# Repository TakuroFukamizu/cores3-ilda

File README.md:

# CoreS3 ILDA

M5Stack CoreS3を使うILDA評価基板と、今後開発する制御ソフトウェアを管理するモノレポです。

## 構成

```text
hardware/rev-a/       Rev.Aの設計説明・部品表
  kicad/             編集するKiCadプロジェクト・回路図・PCB・ローカルライブラリ
firmware/            CoreS3向けファームウェア（未実装）
software/            PC側ツール／アプリ（未実装）
docs/                共通仕様・設計判断
releases/rev-a/       製造・評価時点の生成物と検査記録
build/               作業用の生成物（Git管理外）
```

まず [ハードウェアREADME](hardware/rev-a/README.md) を読んでください。KiCad 10で `hardware/rev-a/kicad/CoreS3_ILDA_RevA.kicad_pro` を開きます。ライブラリはプロジェクト相対参照で同梱しています。

## Git運用

- 回路図・PCB・プロジェクト設定・ライブラリ・BOM・文書・ソースコードをコミットします。
- 通常のGerber、プレビュー、ビルド成果物は `build/` に出力します。KiCadの個人設定、ロック、バックアップは除外します。
- 製造に使用する生成物だけを `releases/<revision>/<date>/` に保存し、その設計と同じコミットで確定します。初回分は2026-10-02の記録です。
- 基板リビジョンを変更する際は `hardware/rev-b/` 等を作り、旧版を保持します。同じリビジョン内の調整はGit履歴で管理します。
- ファームウェアのフレームワーク、依存管理、CI、リモートリポジトリはまだ選定していません。

## 変更後の検証

KiCadでERCとDRC（回路図との一致検査を含む）を再実行し、ゾーンを再フィルして保存してください。CLIをPATHへ設定している場合のPowerShell例：

```powershell
New-Item -ItemType Directory -Force build/rev-a | Out-Null
kicad-cli sch erc --format json -o build/rev-a/ERC.json hardware/rev-a/kicad/CoreS3_ILDA_RevA.kicad_sch
kicad-cli pcb drc --format json --schematic-parity -o build/rev-a/DRC.json hardware/rev-a/kicad/CoreS3_ILDA_RevA.kicad_pcb
```

初回の検査はERC/DRC/未配線/回路図不一致0件ですが、実機動作と機械的嵌合は未検証です。初回電気評価はレーザー未接続で実施してください。制御ソフトウェアには起動時ENABLE Low、DAC初期値、異常時停止の実装が必要です。

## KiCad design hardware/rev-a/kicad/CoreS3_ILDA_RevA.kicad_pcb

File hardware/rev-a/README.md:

# CoreS3 ILDA評価基板 Rev.A

2026-10-02 / KiCad 10.0.6 / 2層・280 × 202.84 mm。手はんだと測定を優先した試作設計です。回路図ERC、PCB DRC、回路図とPCBの一致検査はすべて問題0件。実基板での動作・熱・ノイズ・機械的嵌合は未検証です。

## 開くファイル・発注データ

編集対象はこのフォルダの `kicad/` とBOMです。以下の製造データ・プレビュー・検証結果はリポジトリルートの `releases/rev-a/2026-10-02/` に保存した初回設計時点の記録です。設計変更後は再生成し、古い検査結果を流用しないでください。

- `kicad/CoreS3_ILDA_RevA.kicad_pro` をKiCad 10で開く。回路図はルート＋13子シート。ローカルシンボル・フットプリントを同梱。
- `manufacturing/`：表裏銅箔、表裏マスク、表裏シルク、外形Gerber、PTH/NPTH Excellonドリル、ドリル図。
- `BOM.csv`：部品別明細。`BOM_grouped.csv`：同一部品の集計。DNPは標準構成では未実装。
- `assembly-top.svg`：部品配置・機械形状。`board-top.png`：配線プレビュー。`schematic_svg/`：全回路図プレビュー。
- `verification/`：検査結果と理想DC解析。基板発注設定の目安はFR-4、1.6 mm、2層、銅厚1 oz、両面ソルダーマスク。製造会社の加工条件にも照合してください。

J1のM5-BusはM5Stack公式CoreS3 Module Type Aデータ由来の**表面実装**パターンです。調達候補はM5Stack **A117 / Bus Socket SMD 13.2**。一般的な2×15スルーホールソケットとは互換ではありません。CoreS3本体投影は50×50 mm、位置決め穴と支持穴を設けています。基板の下面へのバス貫通実装はありません。発注前に配置図を原寸印刷し、購入するコネクタ・CoreS3底部と合わせてください。ケース、底部モジュール、スペーサー高さによる干渉は実物確認が必要です。

## 回路構成

MCP4922-E/P×3を3.3V駆動し、共通2.048V基準・共通LDACで6chを更新します。NJM4580DD×4でX/Y差動、RGBのGND基準出力、1.024V中点バッファを構成します。RGBの能動差動には追加NJM4580×2が必要なため、U9/U10と関連部品をオプション実装にしました。

5VからMCW03-05D12で±12Vを生成。AGNDとDGNDは連続した共通GNDプレーンです。DC/DCの出力COMもGNDへ接続するため、この基板全体はガルバニック絶縁されません。SPI配線下のGNDを分断せず、DAC基準とアナログ回路を電源・リレーから分離して配置しています。各ICの電源に100nF、基準に1µFと分散100nFを配置しています。

### 電源・実装

- J2：安定化5V入力。2A供給可能な電源を推奨。極性はシルクと回路図で確認。
- JP1：**1–2＝外部5V（標準）／2–3＝M5-Bus 5V**。同時短絡禁止。標準構成ではCoreS3をUSB等から別途給電します。バス給電はCoreS3側電源容量を確認してから使用。
- F1：基板上の端子台に、絶縁した外付けヒューズホルダー＋T2Aヒューズを接続します。単なるワイヤーで置換しないでください。
- J2/J3/J4/F1の端子台ピッチは**5.00 mm**。5.08 mm品の無理な装着は避け、フットプリントに一致する品を購入。
- R1/R2＝330Ω・2Wは各±12V出力の最小負荷確保用。約36mA／0.44Wを消費するので基板から約5mm浮かせて実装。熱くなります。
- MCW03の各レールは125mA定格。6個のオペアンプを実装した場合、無負荷時の保守的な見積りは負荷抵抗36mA＋オペアンプ54mA＝約90mA/レール。外部負荷分も含めて確認してください。出力コンデンサは各22µF＋デカップリングで、メーカーの容量性負荷上限100µF/レール以内です。
- C4は**プラス側がGND、マイナス側が−12V**。C1は16V以上（25V品も外径6.3mm・ピッチ2.5mmに適合すれば可）、C3/C4は25V以上。
- MCP1501はSOT23-6、Q1はSOT23です。DIP部品のほか、この2点とM5-Busは表面実装が必要です。
- DB25は秋月DMR-25SGG用の専用パターン。外部パネルとねじ／ケーブル支持を併用し、はんだ接合だけにケーブル荷重を掛けないでください。

## CoreS3ピン割当

|機能|GPIO|M5-Busピン|
|---|---:|---:|
|MOSI|G37|7|
|SCK|G36|11|
|CS：X/Y（U1）|G5|8|
|CS：R/G（U2）|G6|21|
|CS：B/I（U3）|G7|22|
|共通LDAC_N|G8|4|
|ENABLE（Highでリレー許可）|G10|2|
|予備、JP2へ|G9|10|
|3V3|—|12|
|5V|—|28|
|GND|—|1、3、5|

LCD・SDとSPIを共有します。LCD CS＝G3、SD CS＝G4を非選択にし、SPIトランザクションを排他制御してください。DAC連続転送中に画面・SDアクセスを割り込ませない構成から評価します。JP2は通常OPEN。

## DAC設定とアナログ出力

MCP4922のVREF A/Bは2.048V、VDDは3.3V。初期設定はSPI mode 0、MSB first、16bit、1MHz。BUF=0（基準入力アンバッファ）、GA=1（利得1）、SHDNビット=1（動作）です。

```text
Channel A command = 0x3000 | (code & 0x0FFF)
Channel B command = 0xB000 | (code & 0x0FFF)
6chを各CSで書き込み → 全CSをHigh → 共通LDACをLow 1µs → High
```

DAC出力はcode×0.5mV、最大code4095で2.0475Vです。ハードウェアSHDN（pin9）はDAC_RUNでプルアップ、JP3は通常OPEN。**JP3短絡によるSHDNはX/Yの中央保持にはなりません**。出力が高インピーダンスとなり、後段で偏った位置へ動く可能性があります。レーザーOFFにはENABLE／ARM回路を使用します。

|出力|公称式・範囲（出力抵抗前）|
|---|---|
|X+/Y+|4.7×(VDAC−1.024V)、約−4.813〜+4.810V|
|X−/Y−|対応する＋出力の反転|
|X/Y差動|約−9.626〜+9.621V、code2048で0V|
|RGB GND基準|2.42×VDAC、0〜4.955V|
|RGB能動差動|＋側1.22×VDAC、−側その反転、差分0〜4.996V|

出力の各線に100Ωを入れています。RGBはリレー出力側に10kΩのプルダウンもあるため、外部無負荷でもDB25側の公称最大差分はGND基準約4.906V／能動差動約4.946Vです。プロジェクタの入力負荷でさらに変わります。抵抗は調達しやすい1%品を基本としたため、中心・利得は実測校正してください。公差を含む最大値は公称値を超え得ます。初期ソフト上限はRGB code3900以下から始め、実測して5V差動を超えない範囲に設定します。

±12V電源に対して、オペアンプ入出力には十分な公称余裕を取っています。ただしデータシートの主な保証条件は±15Vであり、±12Vでの実負荷・過渡応答・クリッピングは実測対象です。DACのセトリング4.5µsは代表値です。25k点/sのシステム性能を保証するものではありません。まず1k点/sで確認し、SPIクロック4〜8MHzなどへの変更後に全ch転送時間とアナログ整定を測定してください。

### RGBジャンパ（電源OFFで変更）

|モード|JP4/JP6/JP8（R/G/B利得）|JP5/JP7/JP9（R/G/B負側）|追加部品|
|---|---|---|---|
|標準：GND基準|OPEN|1–2|なし、U5〜U8の4個|
|能動差動|CLOSED|2–3|U9/U10、C24〜C27、R41〜R49をすべて実装|

利得と負側選択は必ず同時に変更します。GND基準利得のまま負側を反転にすると、差動振幅が過大になります。追加2個のうち余ったアンプはGND追従バッファとして終端しています。

## ARMとDB25

J3に維持型NO接点のARMスイッチ（できればキー式）、J4にNC接点の外部非常停止ループを接続します。ARM閉・非常停止ループ閉・G10 Highのすべてが成立したときだけ、4個の5Vリレーが励磁します（コイル合計約160mA）。G10は外付けプルダウンを設けています。

非励磁時はRGB±をGNDへ接続、シャッターは0V、インターロック4–17は開放です。励磁時にRGBをアナログ出力へ切替、シャッターを5V、インターロックを閉じます。これは起動・手動停止用で、点ごとの高速ブランキングにはRGBのDACデータを使用します。リレーとフライバックダイオードのため停止には遅延があります。

**このRev.Aには独立ウォッチドッグ、走査停止検知、±12V監視、接点溶着監視はありません。CPUがENABLE Highのまま停止した場合や接点故障時の停止は保証できません。** プロジェクタ本体のキー・非常停止・シャッター等も有効にして評価してください。実機のX-RGB 705の入力回路・停止動作は未確認であり、ILDA DB25があることだけで互換性を保証していません。

各使用信号の直前に独立切り離しジャンパを設けています。**初回はJP10〜JP25をすべてOPEN**。未使用DB25ピンはNCです。

|ジャンパ|DB25ピン|信号|
|---|---:|---|
|JP10 / JP18|1 / 14|X+ / X−|
|JP11 / JP19|2 / 15|Y+ / Y−|
|JP12 / JP20|3 / 16|Intensity+ / Intensity−|
|JP13 / JP21|4 / 17|Interlock A / B|
|JP14 / JP22|5 / 18|R+ / R−|
|JP15 / JP23|6 / 19|G+ / G−|
|JP16 / JP24|7 / 20|B+ / B−|
|JP17|12|Shutter|
|JP25|25|信号GND|

第6DACは予備IntensityとしてTP6とJ6 pin1に引き出しています。**Intensity用出力アンプは未実装**です。J6は1＝DAC_I、2＝I+、3＝I−、4＝GNDの外部変換回路接続用。外部回路を追加しない場合はJP12/JP20をOPENのまま使用してください。DAC_IをDB25へ直接接続しないでください。

ケーブルは全ピン直結のILDA用を使用し、両端の性別と導通を確認します。RS-232ヌルモデム／クロスケーブルは使用しません。DB25シェルはこの部品ではPCB接地されません。筐体・シールドの接地は装置側条件に合わせて別途検討します。

## テストポイント

|番号|信号|
|---|---|
|TP1〜TP6|DAC_X、DAC_Y、DAC_R、DAC_G、DAC_B、DAC_I|
|TP7〜TP10|X+、X−、Y+、Y−|
|TP11〜TP16|R+、R−、G+、G−、B+、B−（リレー後、DB25切離し前）|
|TP17 / TP18|VREF 2.048V / VCENTER 1.024V|
|TP19 / TP20|+12V / −12V|
|TP21 / TP22|3V3 / 5V|
|TP23|AGND（共通GND）|
|TP24 / TP25 / TP26|Shutter / ENABLE GPIO / コイル5V|

## 初期評価手順

1. **プロジェクタ・レーザーを接続せずに開始。** はんだ・電源短絡・電解極性・DIP向き・J1嵌合を点検。JP1＝1–2、JP2/JP3＝OPEN、RGB＝GND基準、JP10〜25＝OPEN、ARM＝OFF。
2. 電流制限付き5V電源でJ2へ給電し、5Vと±12Vを確認。R1/R2の発熱を確認し、異常な温度や消費電流があれば停止。CoreS3を別途給電し、3V3、VREF、VCENTERを測定。
3. ファームウェアの最初にENABLE Low、すべてのCSとLDAC Highを設定。表示初期化より先に行う。X/Y＝2048、R/G/B/I＝0を全chへ書き込み、LDACで反映。ARM OFFでRGB±≒0V、シャッター0V、インターロック開放を確認。
4. まだプロジェクタ未接続のままARM ON／ENABLE Highを試験。各DACの0・2048・4095を測定し、X/Y中心と極性、RGB利得を確認。RGB上限を校正。負荷模擬抵抗とオシロスコープで整定・オーバーシュート・ノイズを確認。
5. ENABLE Low、ARM OFF、非常停止、CoreS3リセット・電源断の各操作でRGB接地／シャッターOFF／インターロック開放へ戻るか確認。電源投入順序を変えた試験も実施。差動信号の負側に接地型オシロスコープのGNDクリップを接続しないこと。両チャンネルのGNDは共通GNDとし、差分演算または差動プローブを使う。
6. 電源OFF後に必要なDB25ジャンパを閉じる。Intensityは未使用ならOPEN。X-RGB 705の説明書・ケーブル導通・入力負荷と各停止機能を確認したうえで接続。最初はRGB＝0、XY＝中央。実光を扱う評価は光路を遮蔽し、機器に適した管理下で行う。
7. 小振幅XY（2048±102程度）、低い点更新速度から開始。異常・バッファ欠落時はENABLEをLowへ。安定後に速度・振幅を上げ、中心・最大振幅・RGB黒レベルを保存して校正。

## 検証範囲・調達

`verification/ERC.json` はERC指摘0件、`DRC.json` は違反0件・未接続0件・回路図一致問題0件です。プロジェクト固有の違反除外は使用していません。KiCad標準の無効チェック項目はDRC JSONに列挙されています。`nominal_dc.csv` は実際の接続・抵抗値を使った理想オペアンプの節点解析で、X/YとRGBのDC式を6条件で照合した結果です。実機試験、部品公差解析、過渡SPICE解析、EMC試験、安全認証の代わりではありません。

主要部品は秋月の商品・データシートを確認しました。価格・在庫は変動します。M5-Bus SMDコネクタ、完全一致の5.00mm端子台、外部ARMスイッチ・非常停止・ヒューズなどは別途調達対象です。抵抗の例：10kΩ＝108550、47kΩ＝108560、2.2kΩ＝108540、12kΩ＝108551。寸法・ピッチ・定格もBOMフットプリントと照合してください。

基板外の付属品：5V/2A電源、T2Aヒューズと絶縁ホルダー、維持型NO ARMスイッチ、NC非常停止スイッチ、2.54mmジャンパキャップ、絶縁スペーサー、適合する全ピン直結ILDAケーブル。任意でDIP14ソケット3個、DIP8ソケット4個（差動オプション時6個）。

## 設計時に確認した資料

- [M5Stack CoreS3公式ピンマップ](https://docs.m5stack.com/en/core/CoreS3)
- [公式CoreS3 M5-Bus基板データ](https://github.com/m5stack/M5_Hardware/blob/master/Common/Module_Type_A/Footprints/Module_Type_A_CoreS3_M5_Bus.PcbDoc)
- [M5Stack A117 SMD Bus Socket](https://shop.m5stack.com/products/2-%E2%9C%96-15-pinheader-bus-socket-smd-for-13-2-module-10-sets)
- [MCP4921/4922](https://akizukidenshi.com/goodsaffix/MCP4921_2.pdf)
- [MCP1501](https://akizukidenshi.com/goodsaffix/mcp1501_j.pdf)
- [NJM4580](https://akizukidenshi.com/goodsaffix/NJM4580_j.pdf)
- [MCW03 DC/DC](https://akizukidenshi.com/goodsaffix/MCW03.pdf)
- [DMR-25SGG外形](https://akizukidenshi.com/goodsaffix/DMR-25SGG.pdf)
- [HFD27リレー](https://akizukidenshi.com/goodsaffix/HFD27.pdf)
- [IRLML6344](https://akizukidenshi.com/goodsaffix/irlml6344pbf.pdf)
- [ILDA ISP-99 rev002](https://www.ilda.com/resources/StandardsDocs/ILDA_ISP99_rev002.pdf)

### 2026-10-06 回路図の表示改訂

部品ごとのラベル接続を、機能別に配置した実線主体の回路図へ変更しました。電源、ホスト、基準・中点、DAC、X、Y、R、G、B、ARM、リレー、DB25、オペアンプ電源の13シート＋目次です。テストポイントは各回路へ移動しました。ファイル名は既存参照との連続性のため一部旧名称を維持しています。全160部品・135ネットの接続およびPCBの物理配線は変更していません。PCBは回路図への参照パスだけを同期しています。初回releases配下の回路図プレビューは改訂前の記録です。

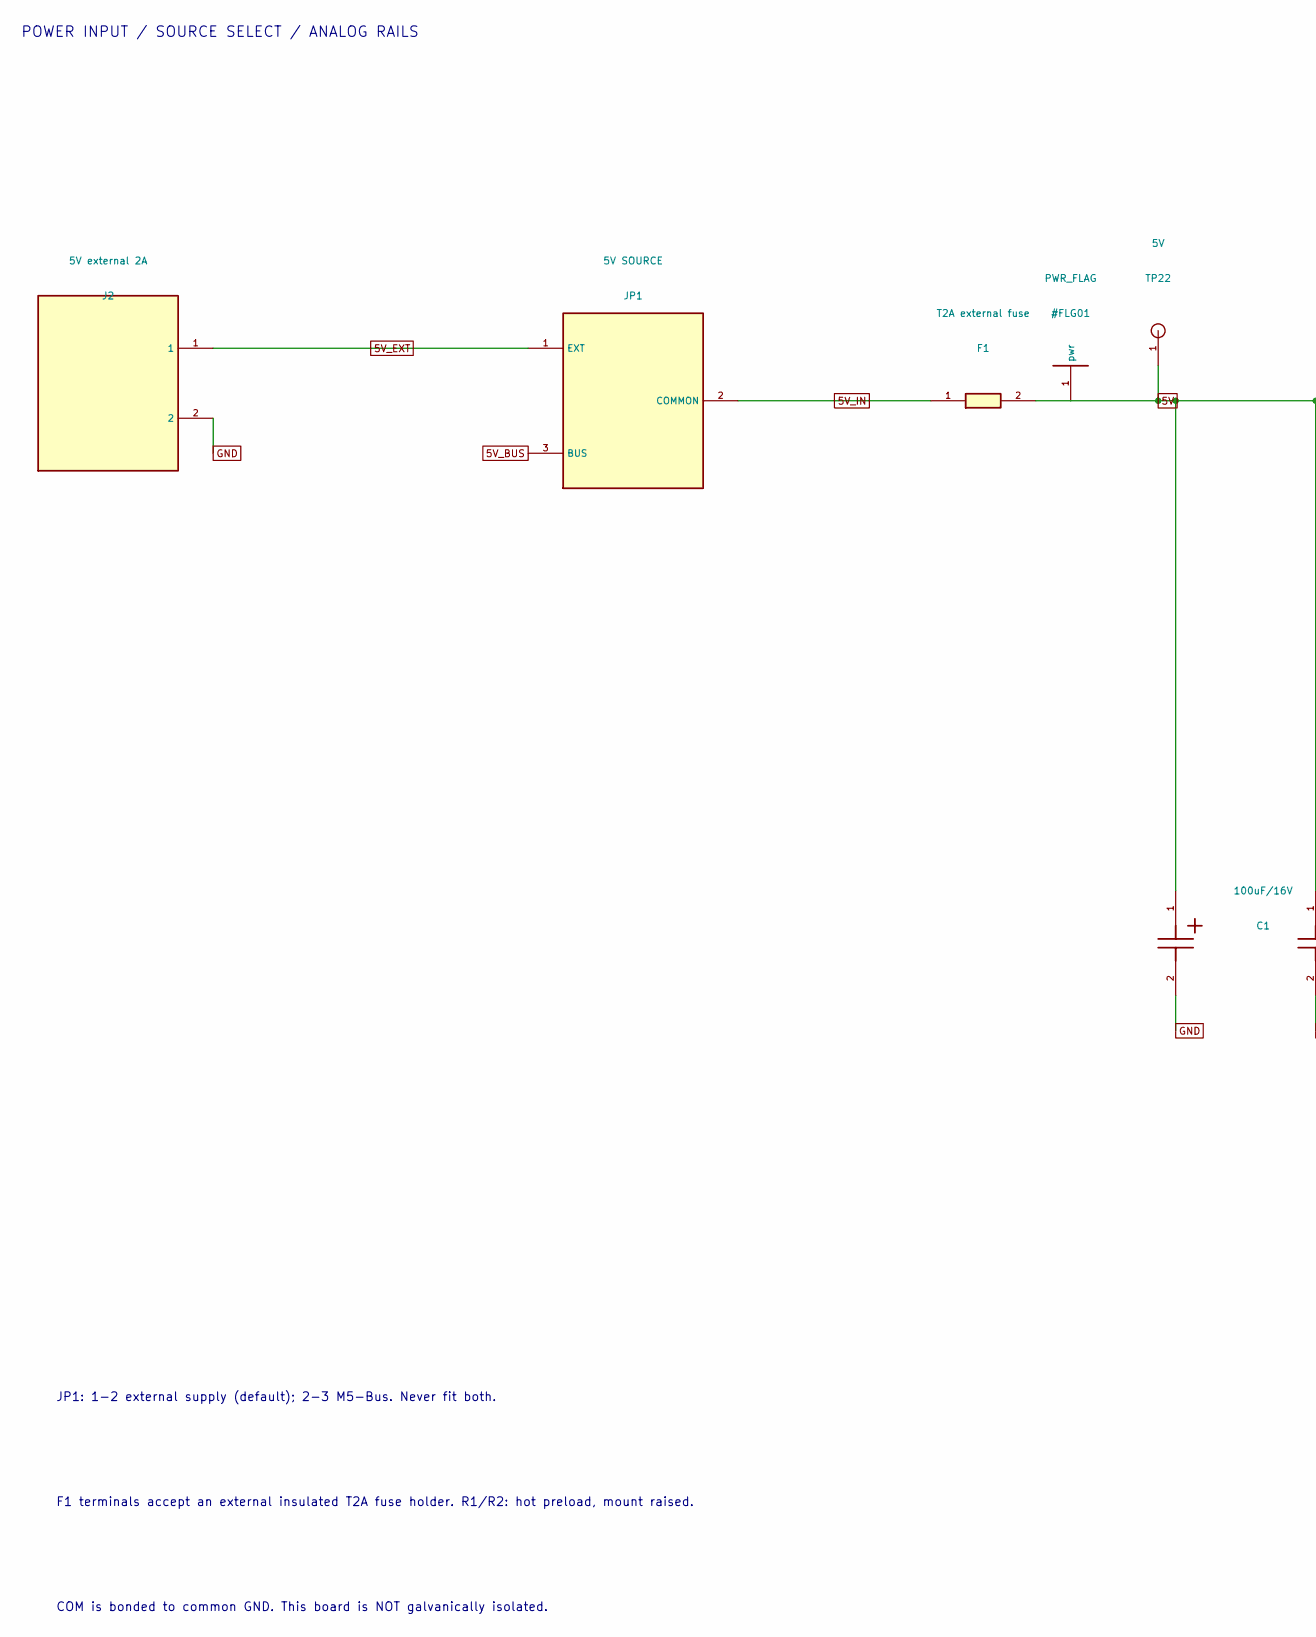
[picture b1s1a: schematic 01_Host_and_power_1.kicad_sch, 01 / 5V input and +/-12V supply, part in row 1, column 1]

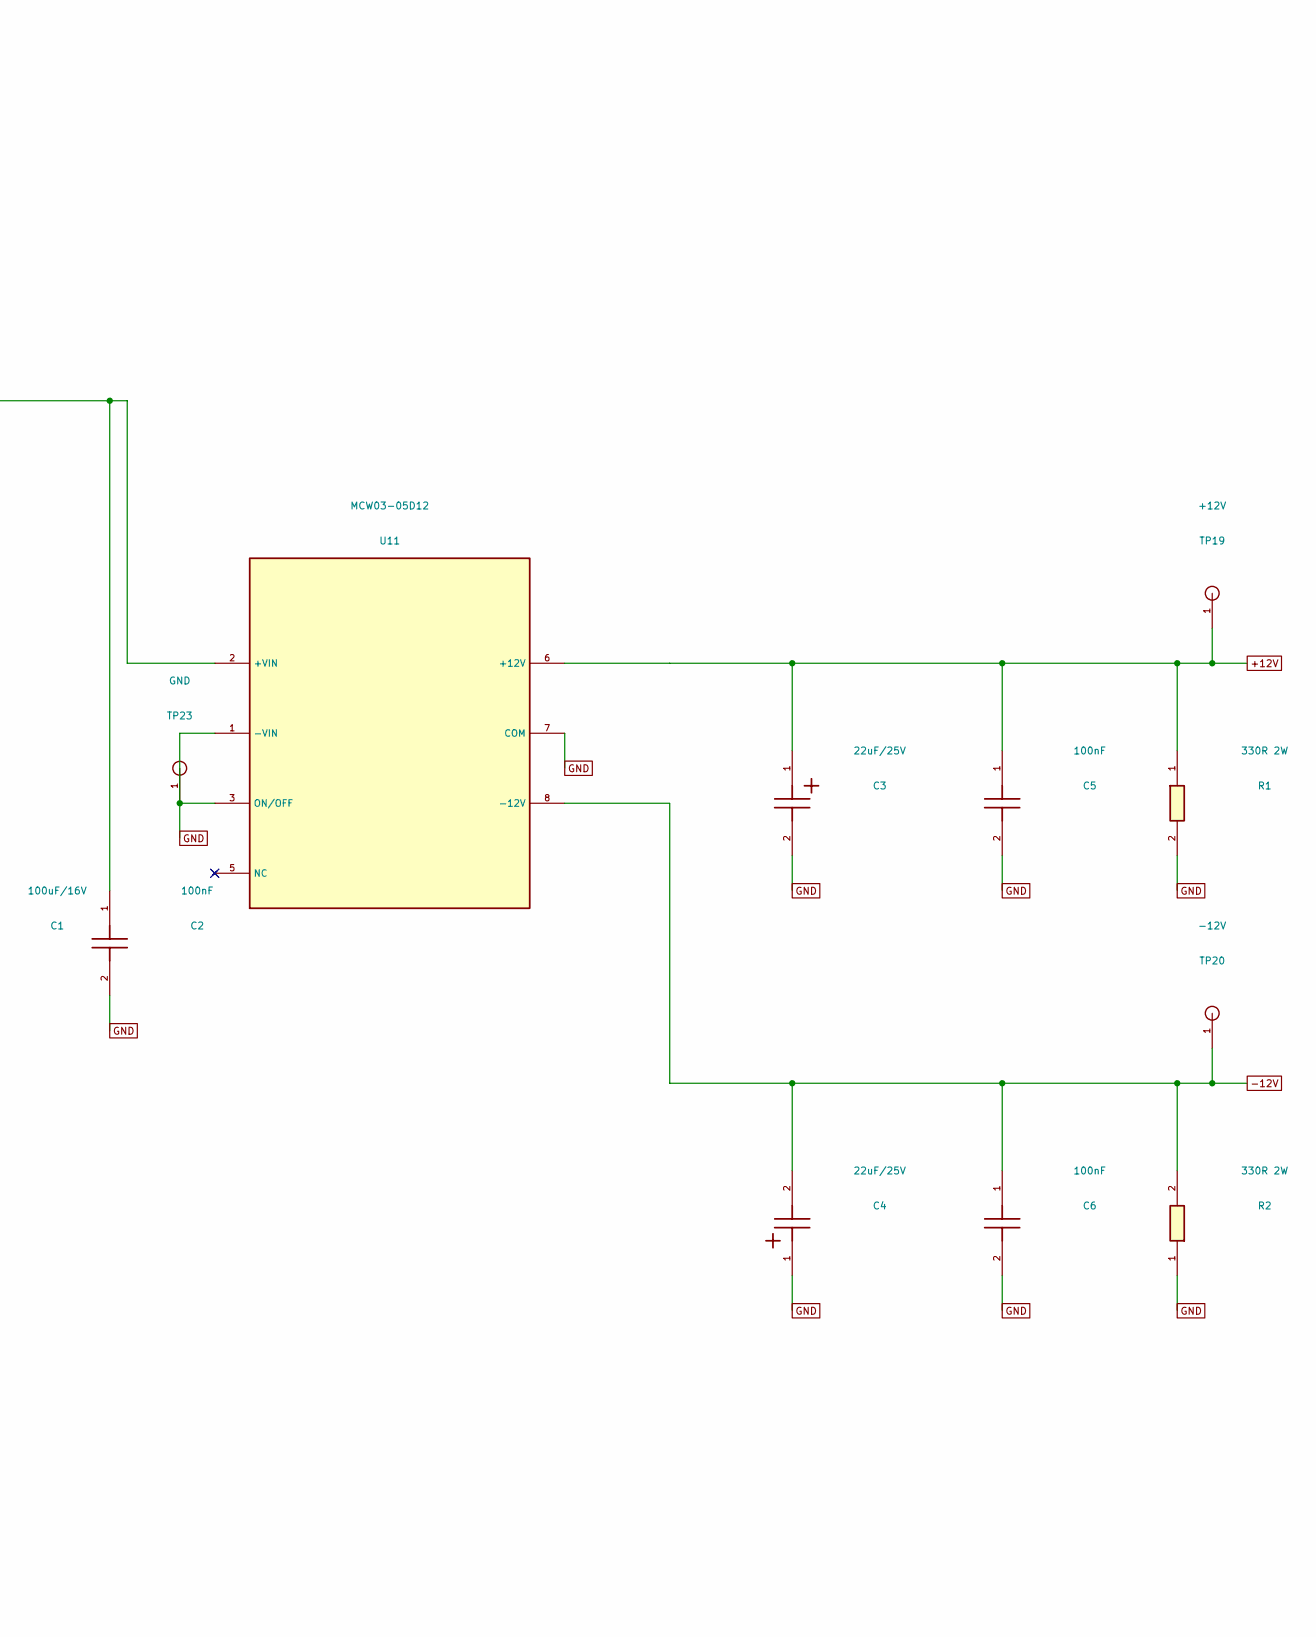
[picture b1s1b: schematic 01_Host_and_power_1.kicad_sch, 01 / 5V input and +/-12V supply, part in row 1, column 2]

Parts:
C1: 100uF/16V; CP_Radial_D6.3mm_P2.50mm
C2, C5, C6: 100nF; C_Disc_D5.0mm_W2.5mm_P5.00mm
C3, C4: 22uF/25V; CP_Radial_D6.3mm_P2.50mm
F1: T2A external fuse; TerminalBlock_Phoenix_MKDS-1,5-2_1x02_P5.00mm_Horizontal
J2: 5V external 2A; TerminalBlock_Phoenix_MKDS-1,5-2_1x02_P5.00mm_Horizontal
JP1: 5V SOURCE; PinHeader_1x03_P2.54mm_Vertical
R1, R2: 330R 2W; R_Axial_DIN0617_L17.0mm_D6.0mm_P20.32mm_Horizontal
TP19: +12V; TestPoint_THTPad_D2.0mm_Drill1.0mm
TP20: -12V; TestPoint_THTPad_D2.0mm_Drill1.0mm
TP22: 5V; TestPoint_THTPad_D2.0mm_Drill1.0mm
TP23: GND; TestPoint_THTPad_D2.0mm_Drill1.0mm
U11: MCW03-05D12; MCW03_SIP8

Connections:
5V: C1.1, C2.1, F1.2, TP22.1, U11.2 (+VIN); also elsewhere on the board
5V_BUS: JP1.3 (BUS); also elsewhere on the board
5V_EXT: J2.1, JP1.1 (EXT)
5V_IN: F1.1, JP1.2 (COMMON)
+12V: C3.1, C5.1, R1.1, TP19.1, U11.6 (+12V); also elsewhere on the board
-12V: C4.2, C6.1, R2.2, TP20.1, U11.8 (-12V); also elsewhere on the board
GND: C1.2, C2.2, C3.2, C4.1, C5.2, C6.2, J2.2, R1.2, R2.1, TP23.1, U11.1 (-VIN), U11.3 (ON/OFF), U11.7 (COM); also elsewhere on the board

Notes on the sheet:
POWER INPUT / SOURCE SELECT / ANALOG RAILS
JP1: 1-2 external supply (default); 2-3 M5-Bus. Never fit both.
F1 terminals accept an external insulated T2A fuse holder. R1/R2: hot preload, mount raised.
COM is bonded to common GND. This board is NOT galvanically isolated.

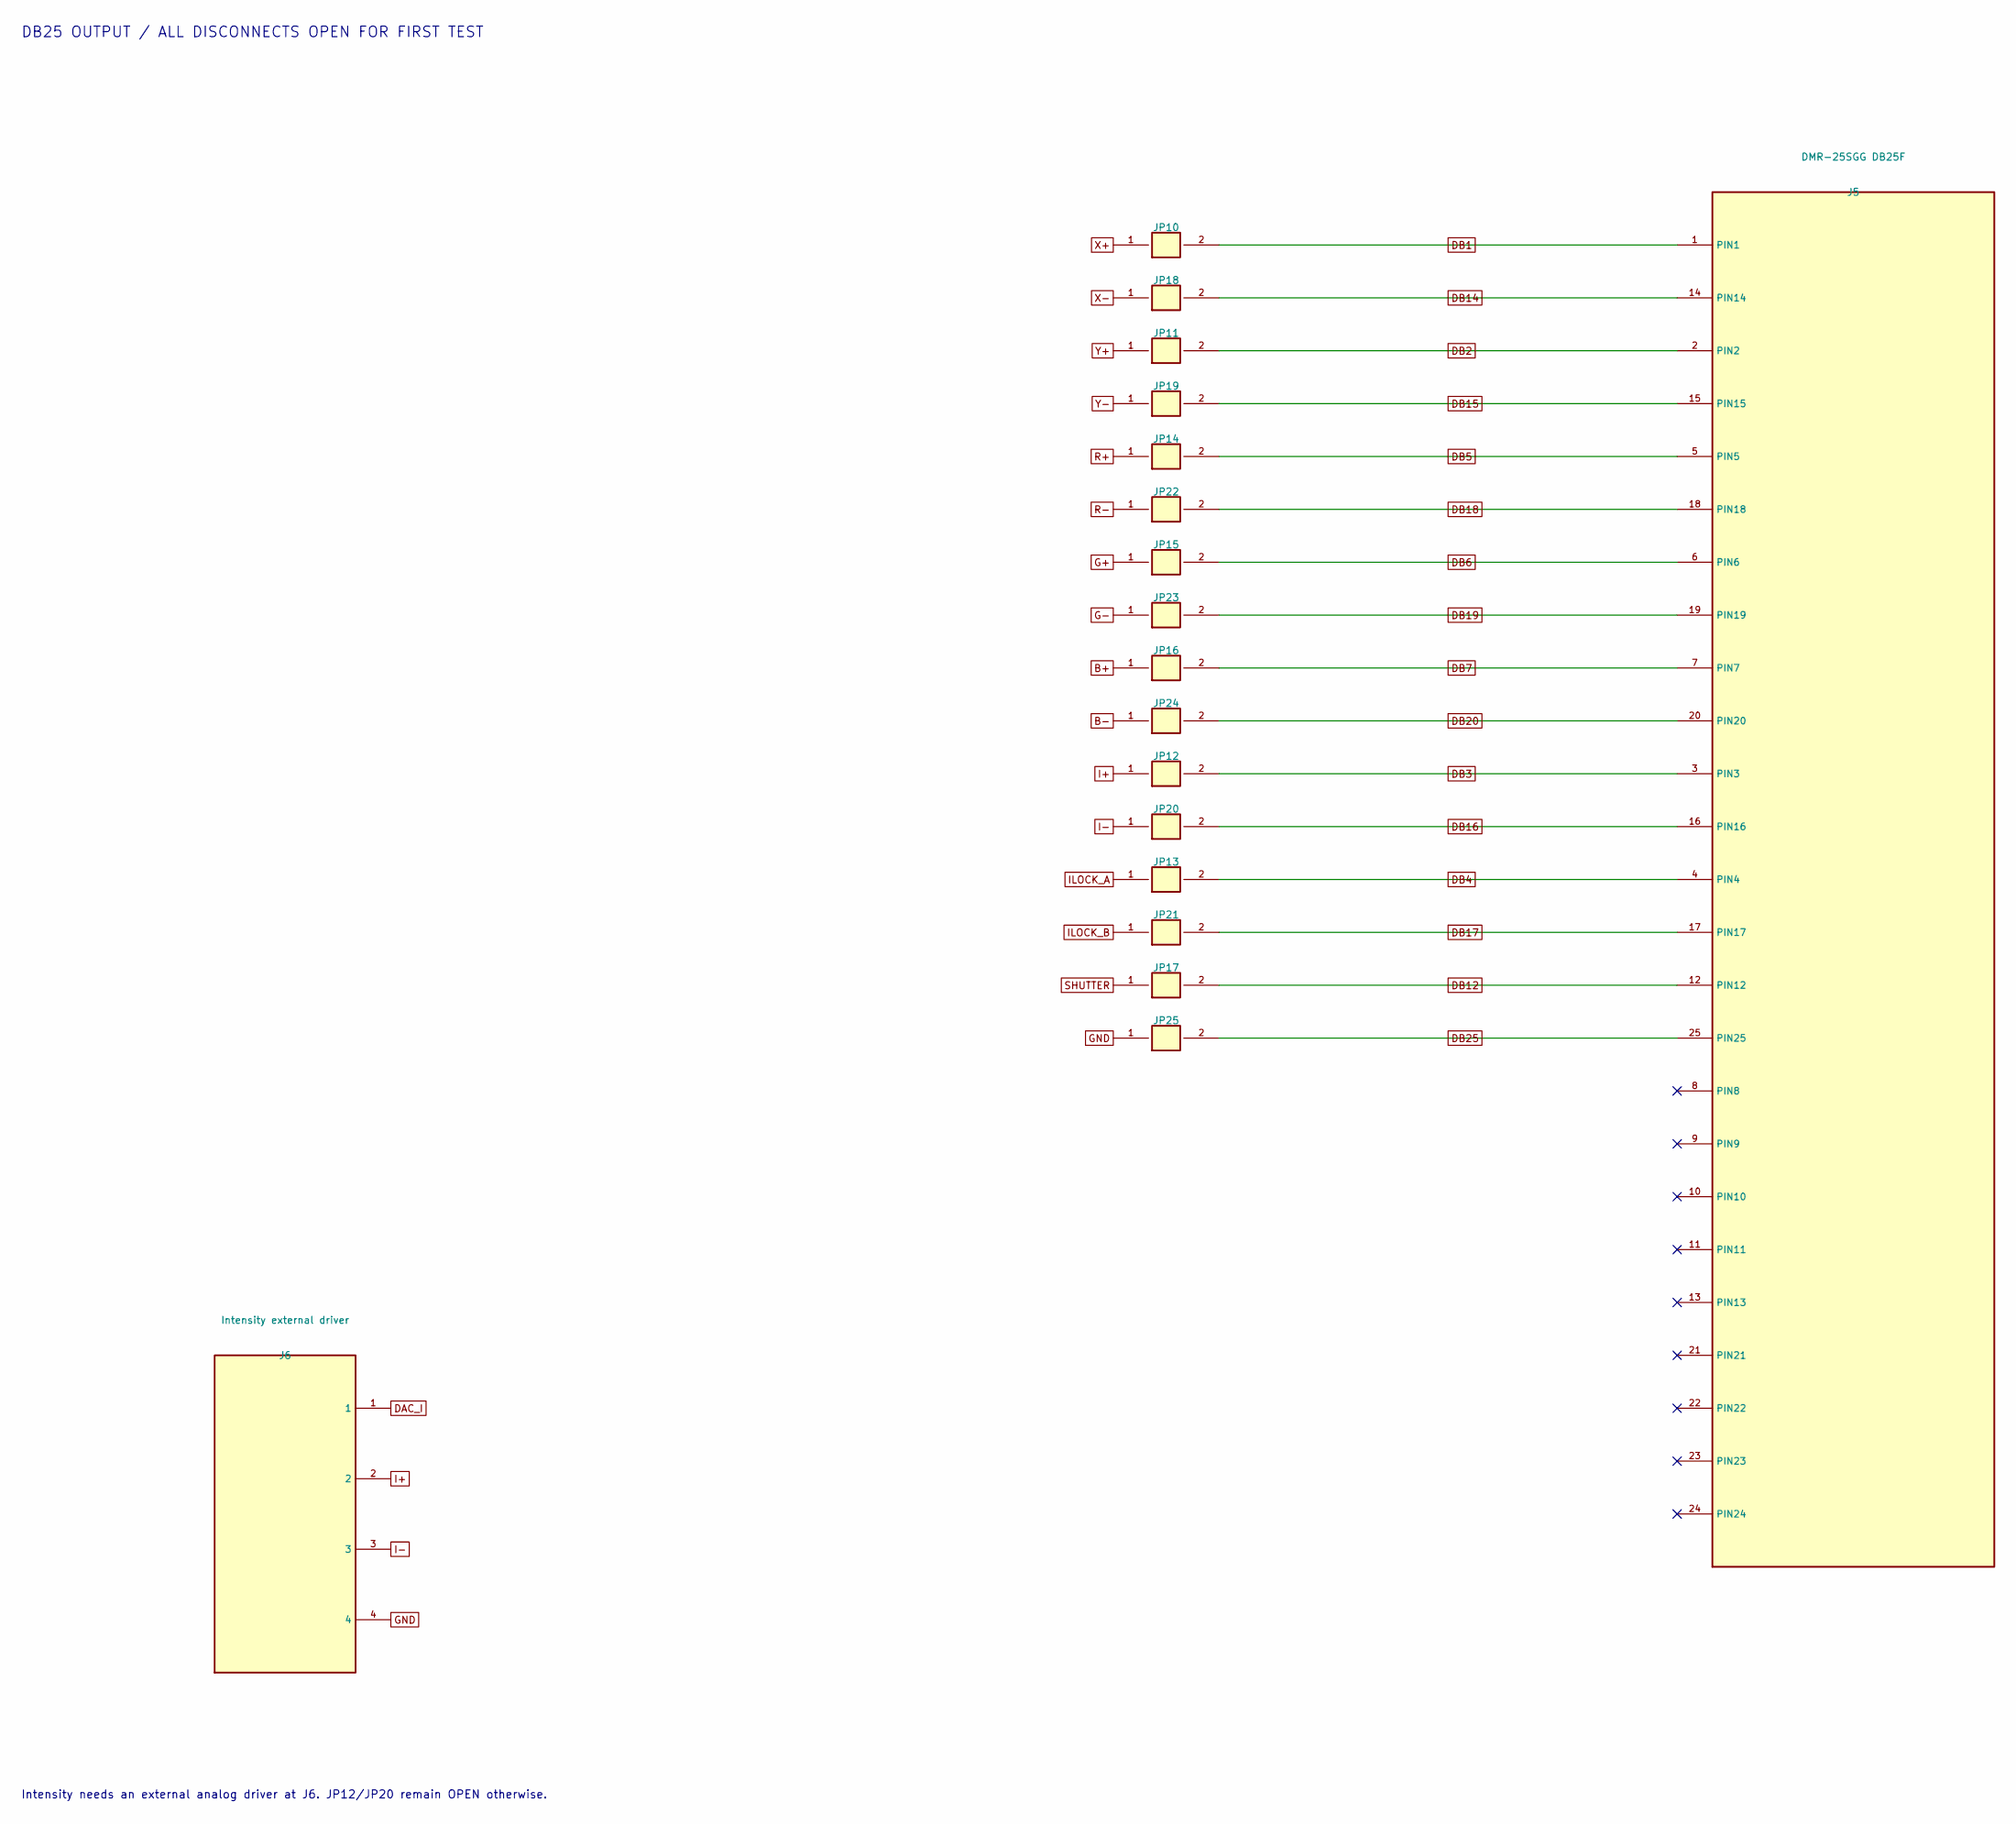
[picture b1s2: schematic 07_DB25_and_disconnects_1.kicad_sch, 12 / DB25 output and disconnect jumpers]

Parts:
J5: DMR-25SGG DB25F; DMR25SGG
J6: Intensity external driver; PinHeader_1x04_P2.54mm_Vertical
JP10: DB1 X+; PinHeader_1x02_P2.54mm_Vertical
JP11: DB2 Y+; PinHeader_1x02_P2.54mm_Vertical
JP12: DB3 I+; PinHeader_1x02_P2.54mm_Vertical
JP13: DB4 ILOCK_A; PinHeader_1x02_P2.54mm_Vertical
JP14: DB5 R+; PinHeader_1x02_P2.54mm_Vertical
JP15: DB6 G+; PinHeader_1x02_P2.54mm_Vertical
JP16: DB7 B+; PinHeader_1x02_P2.54mm_Vertical
JP17: DB12 SHUTTER; PinHeader_1x02_P2.54mm_Vertical
JP18: DB14 X-; PinHeader_1x02_P2.54mm_Vertical
JP19: DB15 Y-; PinHeader_1x02_P2.54mm_Vertical
JP20: DB16 I-; PinHeader_1x02_P2.54mm_Vertical
JP21: DB17 ILOCK_B; PinHeader_1x02_P2.54mm_Vertical
JP22: DB18 R-; PinHeader_1x02_P2.54mm_Vertical
JP23: DB19 G-; PinHeader_1x02_P2.54mm_Vertical
JP24: DB20 B-; PinHeader_1x02_P2.54mm_Vertical
JP25: DB25 GND; PinHeader_1x02_P2.54mm_Vertical

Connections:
B+: JP16.1; also elsewhere on the board
B-: JP24.1; also elsewhere on the board
DAC_I: J6.1; also elsewhere on the board
DB1: J5.1 (PIN1), JP10.2
DB2: J5.2 (PIN2), JP11.2
DB3: J5.3 (PIN3), JP12.2
DB4: J5.4 (PIN4), JP13.2
DB5: J5.5 (PIN5), JP14.2
DB6: J5.6 (PIN6), JP15.2
DB7: J5.7 (PIN7), JP16.2
DB12: J5.12 (PIN12), JP17.2
DB14: J5.14 (PIN14), JP18.2
DB15: J5.15 (PIN15), JP19.2
DB16: J5.16 (PIN16), JP20.2
DB17: J5.17 (PIN17), JP21.2
DB18: J5.18 (PIN18), JP22.2
DB19: J5.19 (PIN19), JP23.2
DB20: J5.20 (PIN20), JP24.2
DB25: J5.25 (PIN25), JP25.2
G+: JP15.1; also elsewhere on the board
G-: JP23.1; also elsewhere on the board
GND: J6.4, JP25.1; also elsewhere on the board
I+: J6.2, JP12.1
I-: J6.3, JP20.1
ILOCK_A: JP13.1; also elsewhere on the board
ILOCK_B: JP21.1; also elsewhere on the board
R+: JP14.1; also elsewhere on the board
R-: JP22.1; also elsewhere on the board
SHUTTER: JP17.1; also elsewhere on the board
X+: JP10.1; also elsewhere on the board
X-: JP18.1; also elsewhere on the board
Y+: JP11.1; also elsewhere on the board
Y-: JP19.1; also elsewhere on the board

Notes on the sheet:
DB25 OUTPUT / ALL DISCONNECTS OPEN FOR FIRST TEST
Intensity needs an external analog driver at J6. JP12/JP20 remain OPEN otherwise.

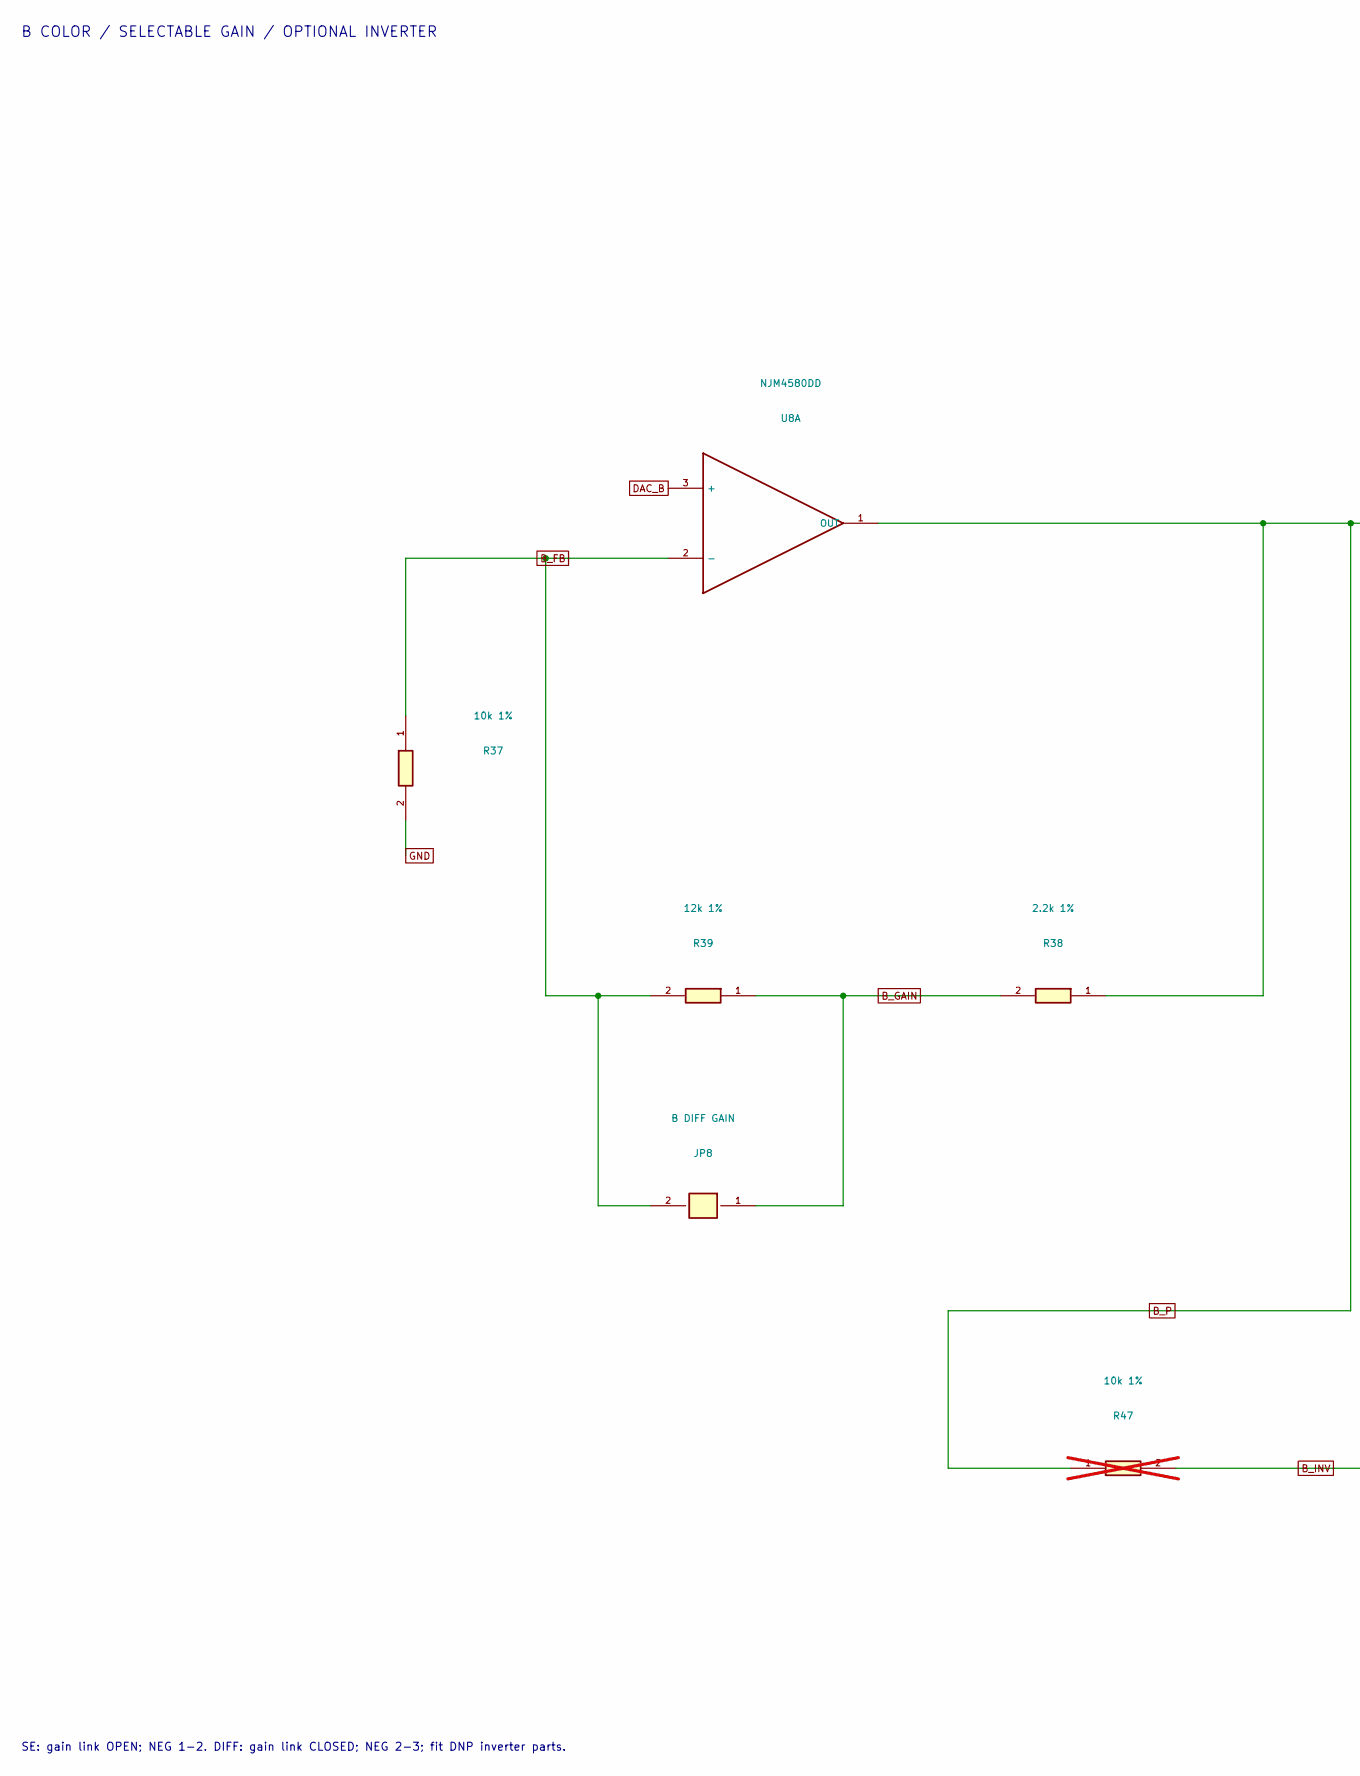
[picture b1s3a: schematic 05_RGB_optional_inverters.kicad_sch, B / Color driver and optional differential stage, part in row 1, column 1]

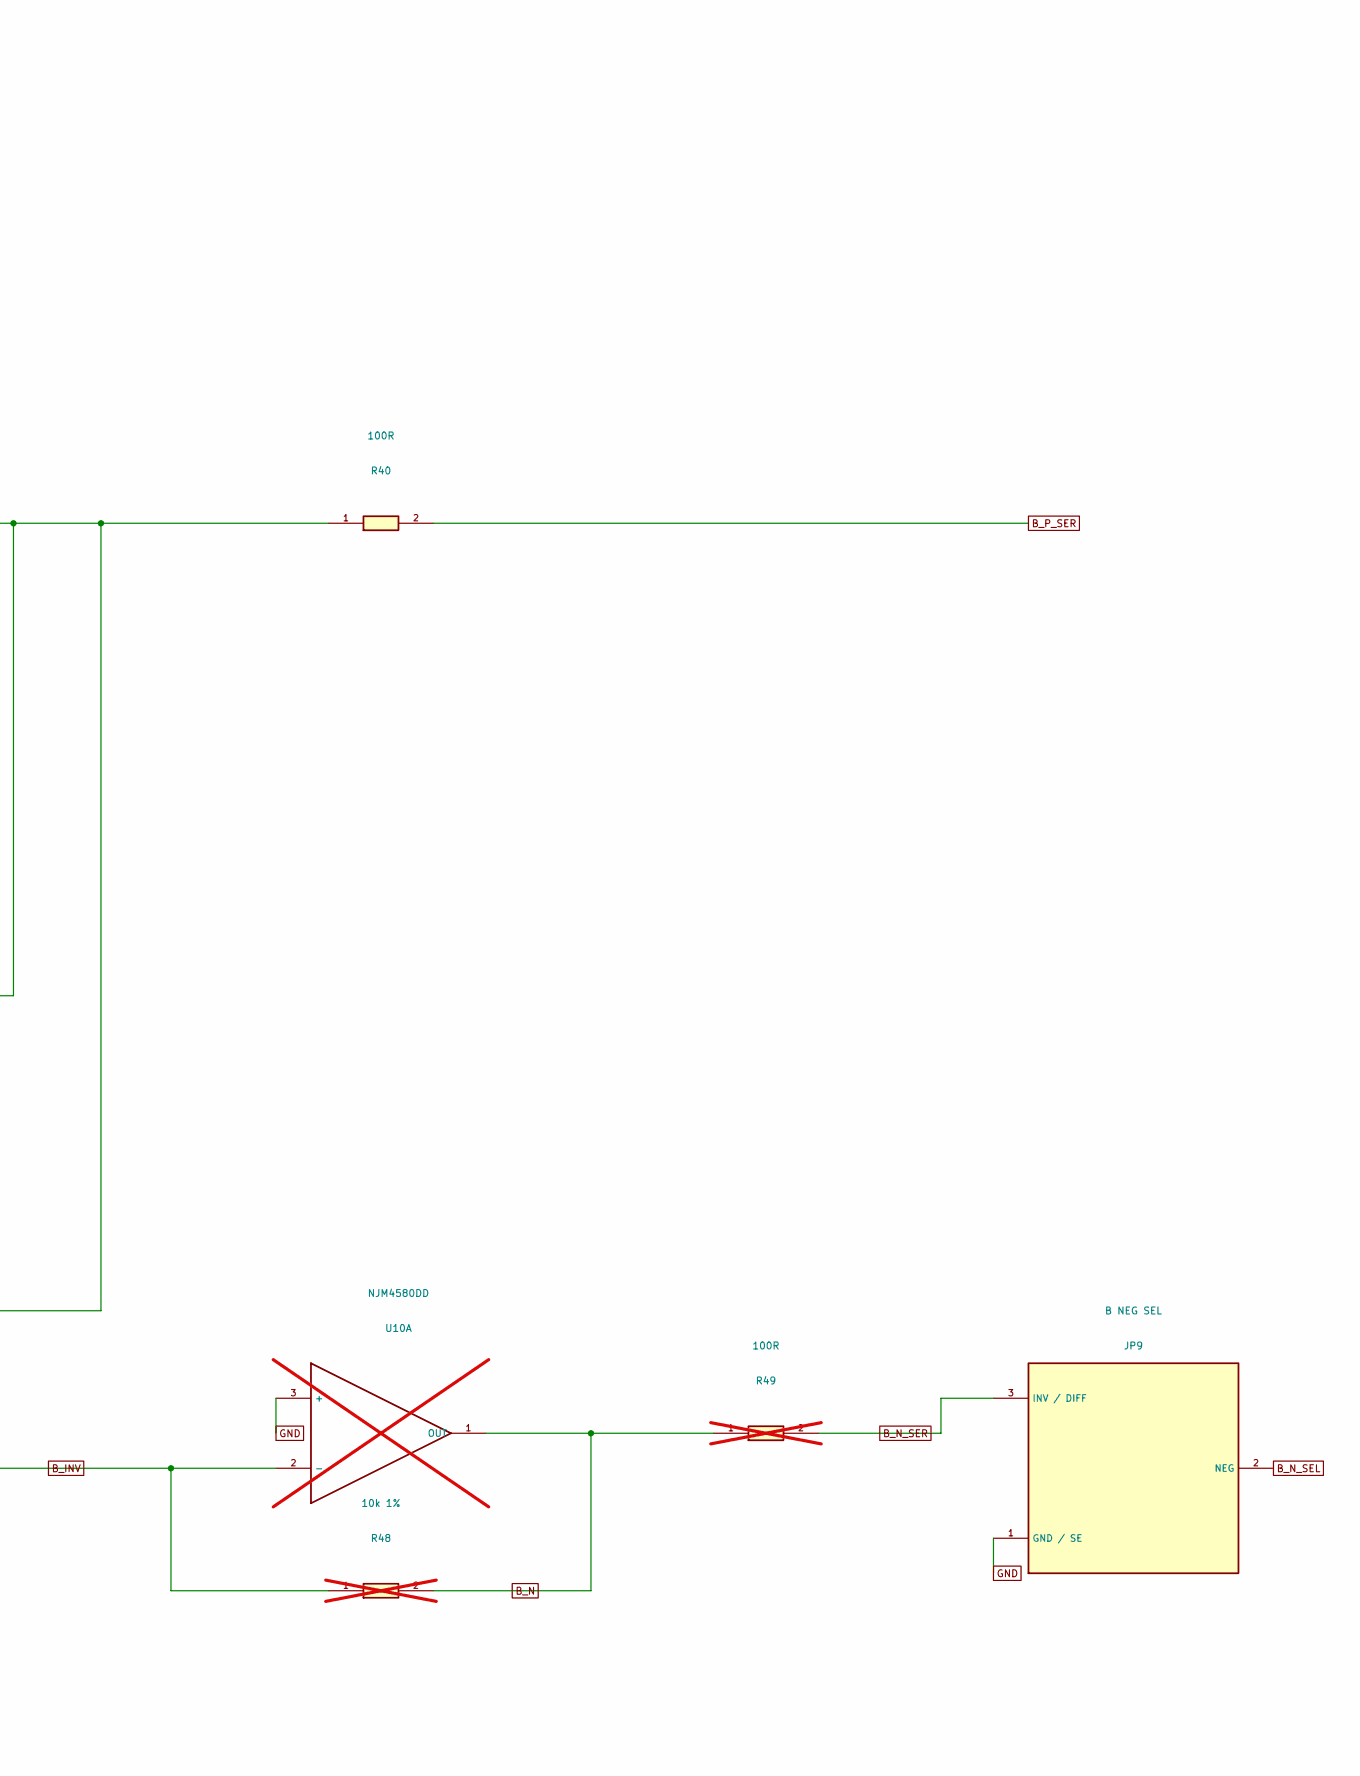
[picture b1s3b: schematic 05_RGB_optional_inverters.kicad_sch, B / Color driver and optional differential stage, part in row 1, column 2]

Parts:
JP8: B DIFF GAIN; PinHeader_1x02_P2.54mm_Vertical
JP9: B NEG SEL; PinHeader_1x03_P2.54mm_Vertical
R37: 10k 1%; R_Axial_DIN0207_L6.3mm_D2.5mm_P10.16mm_Horizontal
R38: 2.2k 1%; R_Axial_DIN0207_L6.3mm_D2.5mm_P10.16mm_Horizontal
R39: 12k 1%; R_Axial_DIN0207_L6.3mm_D2.5mm_P10.16mm_Horizontal
R40: 100R; R_Axial_DIN0207_L6.3mm_D2.5mm_P10.16mm_Horizontal
R47, R48: 10k 1%; R_Axial_DIN0207_L6.3mm_D2.5mm_P10.16mm_Horizontal; not fitted
R49: 100R; R_Axial_DIN0207_L6.3mm_D2.5mm_P10.16mm_Horizontal; not fitted
U8: NJM4580DD; DIP-8_W7.62mm
U10: NJM4580DD; DIP-8_W7.62mm; not fitted

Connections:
B_FB: JP8.2, R37.1, R39.2, U8.2 (-)
B_GAIN: JP8.1, R38.2, R39.1
B_INV: R47.2, R48.1, U10.2 (-)
B_N: R48.2, R49.1, U10.1 (OUT)
B_N_SEL: JP9.2 (NEG); also elsewhere on the board
B_N_SER: JP9.3 (INV / DIFF), R49.2
B_P: R38.1, R40.1, R47.1, U8.1 (OUT)
B_P_SER: R40.2; also elsewhere on the board
DAC_B: U8.3 (+); also elsewhere on the board
GND: JP9.1 (GND / SE), R37.2, U10.3 (+); also elsewhere on the board

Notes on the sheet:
B COLOR / SELECTABLE GAIN / OPTIONAL INVERTER
SE: gain link OPEN; NEG 1-2. DIFF: gain link CLOSED; NEG 2-3; fit DNP inverter parts.
